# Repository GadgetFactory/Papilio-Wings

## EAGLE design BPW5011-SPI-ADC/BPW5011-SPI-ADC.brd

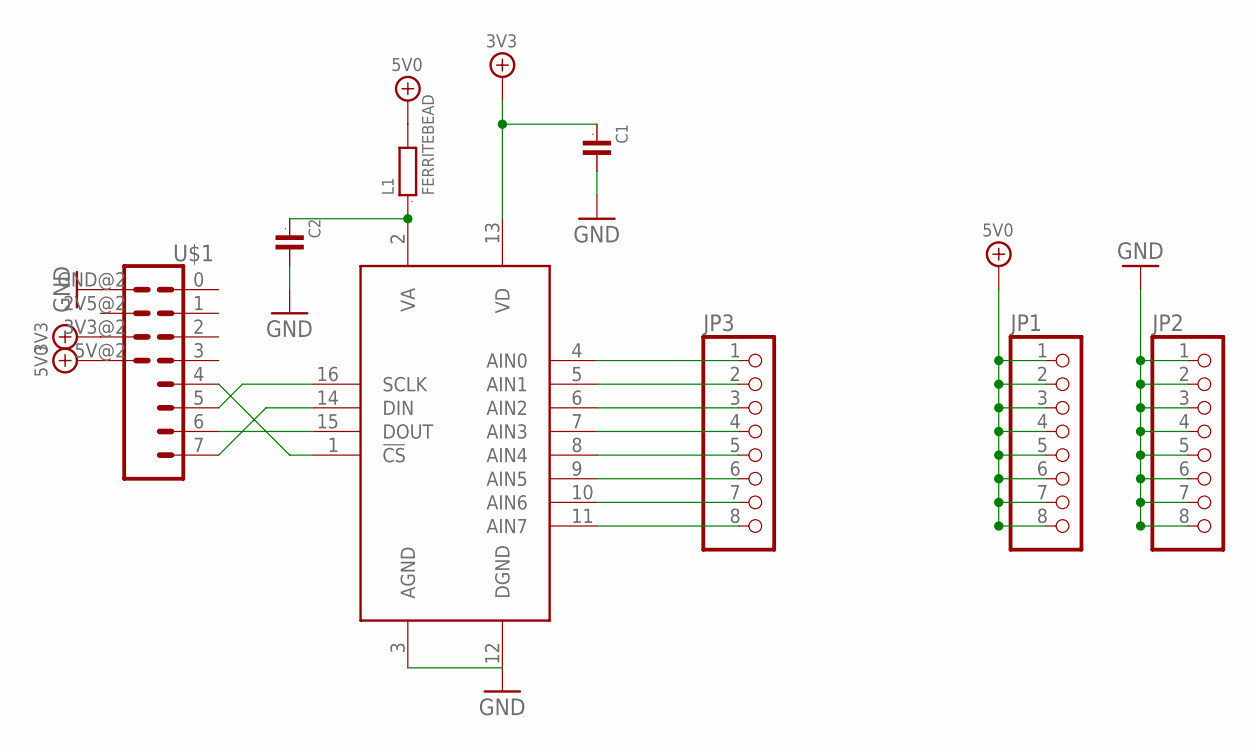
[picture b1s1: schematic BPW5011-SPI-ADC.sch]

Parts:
C1, C2: C0603; 0603
JP1, JP2, JP3: PINHD-1X8; 1X08
L1: FERRITEBEAD; 0603
U1: ADC088S102CIMT; TSSOP16
U$1: WING8WING8_NOHOLES; WINGSIDE_8BIT_NOHOLES

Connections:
3V3: C1.1, U1.13 (VD), U$1.3V3@2 (3V3)
5V0: JP1.1, JP1.2, JP1.3, JP1.4, JP1.5, JP1.6, JP1.7, JP1.8, L1.2, U$1.5V@2 (5V)
GND: C1.2, C2.2, JP2.1, JP2.2, JP2.3, JP2.4, JP2.5, JP2.6, JP2.7, JP2.8, U1.3 (AGND), U1.12 (DGND), U$1.GND@2 (GND)
unnamed: JP3.1, U1.4 (AIN0)
unnamed: JP3.2, U1.5 (AIN1)
unnamed: JP3.3, U1.6 (AIN2)
unnamed: JP3.4, U1.7 (AIN3)
unnamed: JP3.5, U1.8 (AIN4)
unnamed: JP3.6, U1.9 (AIN5)
unnamed: JP3.7, U1.10 (AIN6)
unnamed: JP3.8, U1.11 (AIN7)
unnamed: C2.1, L1.1, U1.2 (VA)
unnamed: U1.1 (!CS), U$1.4 (5)
unnamed: U1.15 (DOUT), U$1.6 (7)
unnamed: U1.16 (SCLK), U$1.5 (6)
unnamed: U1.14 (DIN), U$1.7 (8)

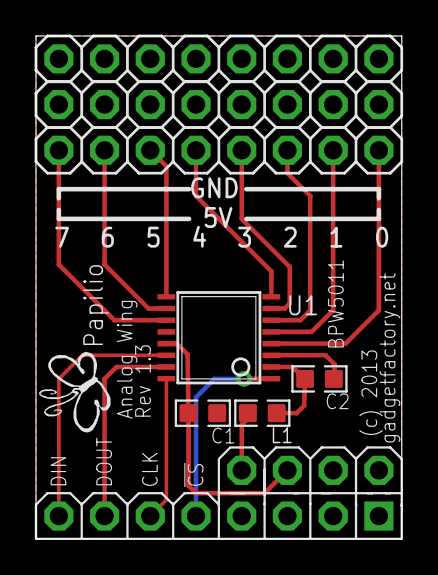
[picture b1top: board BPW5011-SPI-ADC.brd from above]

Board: 2 copper layers, 20.3 x 27.9 mm, 9 parts (0 on the bottom side), 16 nets.

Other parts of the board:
U$2: GADGETFACTORY_LOGO

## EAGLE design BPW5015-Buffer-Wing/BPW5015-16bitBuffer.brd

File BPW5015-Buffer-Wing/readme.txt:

BPW5015 Buffer Wing Manufacturing Package - Current Version 1.3

Special assembly instructions:
-Use RED for the PCB color.
-Critical! - Must use the correct 5V TI chip for this to work:
http://www.digikey.com/product-detail/en/SN74CBT16245DGGR/296-6402-1-ND/377867
Tested on 7/30/2014

CHANGELOG
8/22/2014 Version 1.3

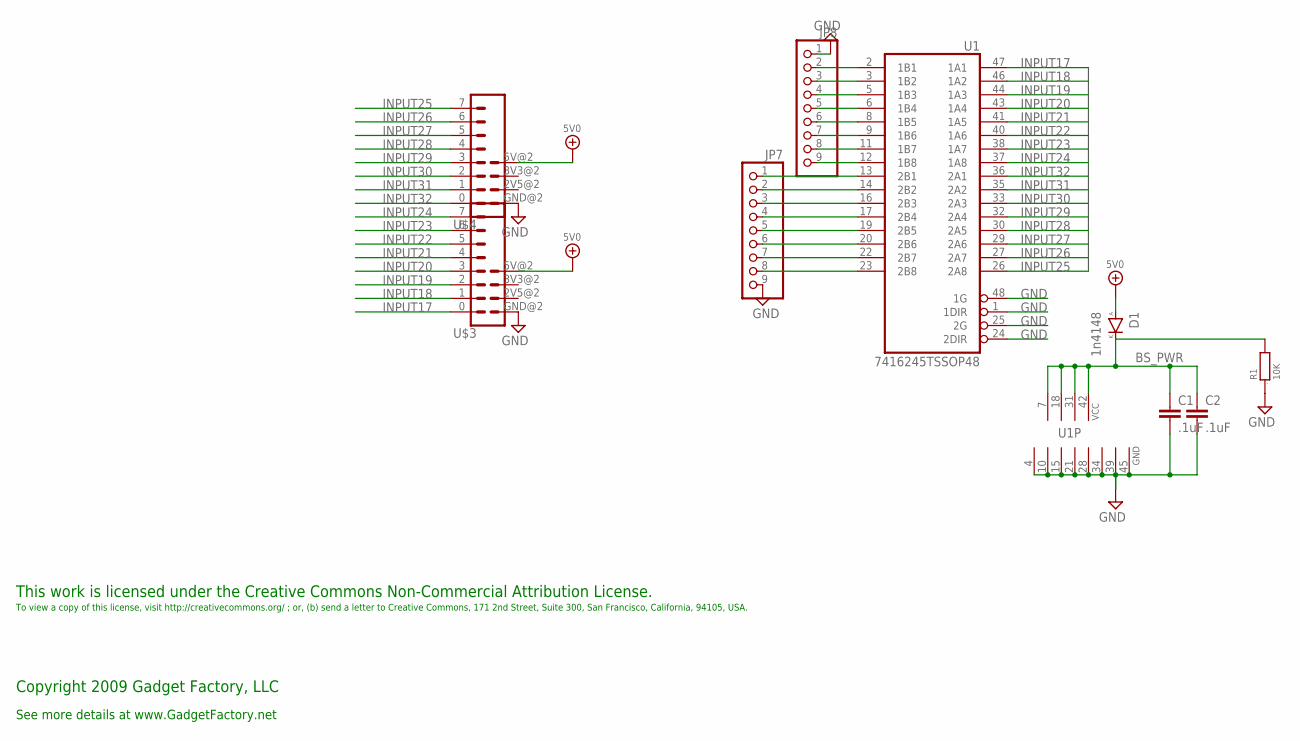
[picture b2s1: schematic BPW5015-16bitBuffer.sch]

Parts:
C1, C2: .1uF; C0603
D1: 1n4148; SOD323
JP7, JP8: PINHD-1X9; 1X09
R1: 10K; 0603
U1: 7416245TSSOP48; TSSOP48
U$3, U$4: WING8; WINGSIDE_8BIT

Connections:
5V0: D1.A, U$3.5V@2 (5V), U$4.5V@2 (5V)
BS_PWR: C1.1, C2.1, D1.K, R1.2, U1.7 (VCC), U1.18 (VCC), U1.31 (VCC), U1.42 (VCC)
GND: C1.2, C2.2, JP7.9, JP8.1, R1.1, U1.1 (1DIR), U1.4 (GND), U1.10 (GND), U1.15 (GND), U1.21 (GND), U1.24 (2DIR), U1.25 (2G), U1.28 (GND), U1.34 (GND), U1.39 (GND), U1.45 (GND), U1.48 (1G), U$3.GND@2 (GND), U$4.GND@2 (GND)
INPUT17: U1.47 (1A1), U$3.0 (1)
INPUT18: U1.46 (1A2), U$3.1 (2)
INPUT19: U1.44 (1A3), U$3.2 (3)
INPUT20: U1.43 (1A4), U$3.3 (4)
INPUT21: U1.41 (1A5), U$3.4 (5)
INPUT22: U1.40 (1A6), U$3.5 (6)
INPUT23: U1.38 (1A7), U$3.6 (7)
INPUT24: U1.37 (1A8), U$3.7 (8)
INPUT25: U1.26 (2A8), U$4.7 (8)
INPUT26: U1.27 (2A7), U$4.6 (7)
INPUT27: U1.29 (2A6), U$4.5 (6)
INPUT28: U1.30 (2A5), U$4.4 (5)
INPUT29: U1.32 (2A4), U$4.3 (4)
INPUT30: U1.33 (2A3), U$4.2 (3)
INPUT31: U1.35 (2A2), U$4.1 (2)
INPUT32: U1.36 (2A1), U$4.0 (1)
unnamed: JP8.9, U1.12 (1B8)
unnamed: JP8.8, U1.11 (1B7)
unnamed: JP8.7, U1.9 (1B6)
unnamed: JP8.6, U1.8 (1B5)
unnamed: JP8.5, U1.6 (1B4)
unnamed: JP8.4, U1.5 (1B3)
unnamed: JP8.3, U1.3 (1B2)
unnamed: JP8.2, U1.2 (1B1)
unnamed: JP7.1, U1.13 (2B1)
unnamed: JP7.2, U1.14 (2B2)
unnamed: JP7.3, U1.16 (2B3)
unnamed: JP7.4, U1.17 (2B4)
unnamed: JP7.5, U1.19 (2B5)
unnamed: JP7.6, U1.20 (2B6)
unnamed: JP7.7, U1.22 (2B7)
unnamed: JP7.8, U1.23 (2B8)

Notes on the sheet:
This work is licensed under the Creative Commons Non-Commercial Attribution License.
To view a copy of this license, visit http://creativecommons.org/ ; or, (b) send a letter to Creative Commons, 171 2nd Street, Suite 300, San Francisco, California, 94105, USA.
Copyright 2009 Gadget Factory, LLC
See more details at www.GadgetFactory.net

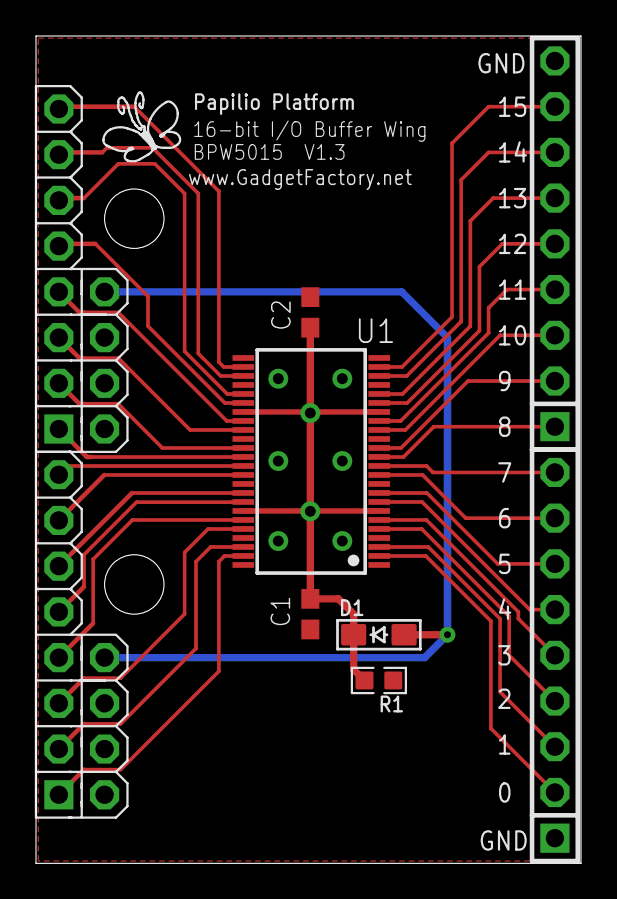
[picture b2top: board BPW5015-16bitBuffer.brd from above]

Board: 2 copper layers, 30.3 x 46.0 mm, 10 parts (0 on the bottom side), 35 nets.

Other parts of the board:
U$1: BUTTERFLY_LOGO

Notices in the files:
BPW5011-SPI-ADC/BPW5011-SPI-ADC.brd:
(c) 2013
